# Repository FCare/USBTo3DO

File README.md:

# USBTo3DO
Connecting USB controller to the 3do

## Goal of the project
Plug a set of modern controllers to an original 3DO to emulate D-Pad, FlightStick and mouse.
Still support original 3DO controllers using daisy chain.

## License
The full project is delivered under MIT License.
You can fork, build, even sell this if you wants to.

## Need more info
I may organize some batches for interested users which can not build it themselves.
If you are interested, you can mail to usb23do@gmail.com
Be sure that you can have one the controller listed here. Adding more controller is not guaranteed.

## Supported controllers
 - **D-Pad**
	 - Any HID Gamepad/joystick class device shall work with a default mapping.
	 - Xbox360 wired controllers is supported.
	 - Xbox360 wireless controller is supported using a USB wireless adapter (https://aliexpress.com/item/1005004013649915.html)
	  > As button layout is not standard, a [specific mapper can be implemented](#dedicated_mapping).
 - **Mouse**
	 - Any USB mouse with an HID descriptor might work as mouse.
 - **FlightStick**
	  > As there is no way from the HID decriptor to determine if a controler is a flightstick or a standard controler, a [specific mapper has to be implemented](#dedicated_mapping)
 - **Wheel**
	  > Even if 3DO did not get any wheel controller, USB23DO support some controler as wheel (no throttle), mostly for Need For speed game. This support requires a [specific mapper to be implemented](#dedicated_mapping)

## List of tested USB controllers
 - **D-Pad**
   - Sixaxis PS3 controller (Wired) (https://en.wikipedia.org/wiki/Sixaxis)
   - DualShock4 PS4 controller (Wired) (https://fr.wikipedia.org/wiki/DualShock)
   - Xbox 360 wirless controllers using a USB PC receiver (https://aliexpress.com/item/1005004013649915.html)
   - 8BitDo M30 controller (https://www.8bitdo.com/m30/)
   - Retrobit Saturn controller (https://retro-bit.com/sega-collaboration/#saturn2-4)
   - Classical WII controllers with USB adapter (https://www.mayflash.com/product/showproduct.php?id=21)
   - Orignial sega saturn controller with adapter (https://www.mayflash.com/product/showproduct.php?id=20)
   - Known issues on 8bitDo USB wireless adapter2, Logitech gamepad F310 and 8bitDo SN30 pro (https://www.8bitdo.com/sn30-pro-usb-gamepad/)
 - **Mouse**
   - a large set of USB mouse
 - **FlightStick**
   - Thrustmaster T-Flight Hotas X (https://shop.thrustmaster.com/fr_fr/t-flight-hotas-x.html)
   - Thrustmaster T-Flight Stick X (https://www.thrustmaster.com/fr-fr/products/t-flight-stick-x)
   - Logitech Extreme 3D Pro (https://www.logitechg.com/fr-fr/products/space/extreme-3d-pro-joystick.942-000031.html)
 - **Wheel**
   - Thrustmaster T80 (https://www.thrustmaster.com/fr-fr/products/t80-ferrari-488-gtb-edition)
 
As of today, it does not support USB HUB. So if you are using a wired controller, you will need an adapter per wired controller. When you plug a USB adpater able to handle multiple controller (like wii adapater, saturn adapter or Xbox360 wireless receiver), then you can connect multiples controllers.

In case you installed the daisy chain connector, you can plug other USB adaptors or original controllers, Daisy chain will work.

## Videos
- [**D-Pad**](https://www.youtube.com/watch?v=yVEVkbPncLI&t=19)
- [**Mouse**](https://www.youtube.com/watch?v=dmMzbSZ1rbM&t=14)
- [**FlightStick**](https://www.youtube.com/watch?v=JpNO-n8_HC8&t=34)
- [**Wheel**](https://www.youtube.com/watch?v=EjhhHNndm9Q)

## What is required
 - PCB as provided in this git project. (You can order to shops like [JLCPCB](https://jlcpcb.com) using the [gerber files provided](https://github.com/FCare/USBTo3DO/blob/release/PCB/Gerber/USB23DO_2022-11-05.zip)
 - One femelle DB9 connector (to connect to the 3do or to the previous controller)
 - One male DB9 (optional) to continue the controller daisy chain
 - One Waveshare rp2040 zero (https://www.waveshare.com/rp2040-zero.htm)
 - a 4 way level shihter (https://aliexpress.com/item/32771873030.html)
 - a 4.7uF - 10v capacitor
 - a DB9 cable extension (https://aliexpress.com/item/4000095438635.html)

Here is a picture of the v1.1 PCB:  

## How to add a dedicated mapping
In order to add a specific mapping, you have to edit hid_gamepad.c or vendor_gamepad.c and add in the map array the VID, PID and corresponding mapping function. Once this is done, you have to compile a new FW and update the RP2040 device.

## How to compile
 - Tested on UBUNTU 20.04

 `git clone https://github.com/FCare/USBTo3DO.git`  
 `cd USBTo3DO`  
 `git submodule update --init --recursive`  
 `mkdir build;cd build`  
 `cmake ../`  
 `make -j16`  
 
 then flash RP2040 with the built uf2 file.

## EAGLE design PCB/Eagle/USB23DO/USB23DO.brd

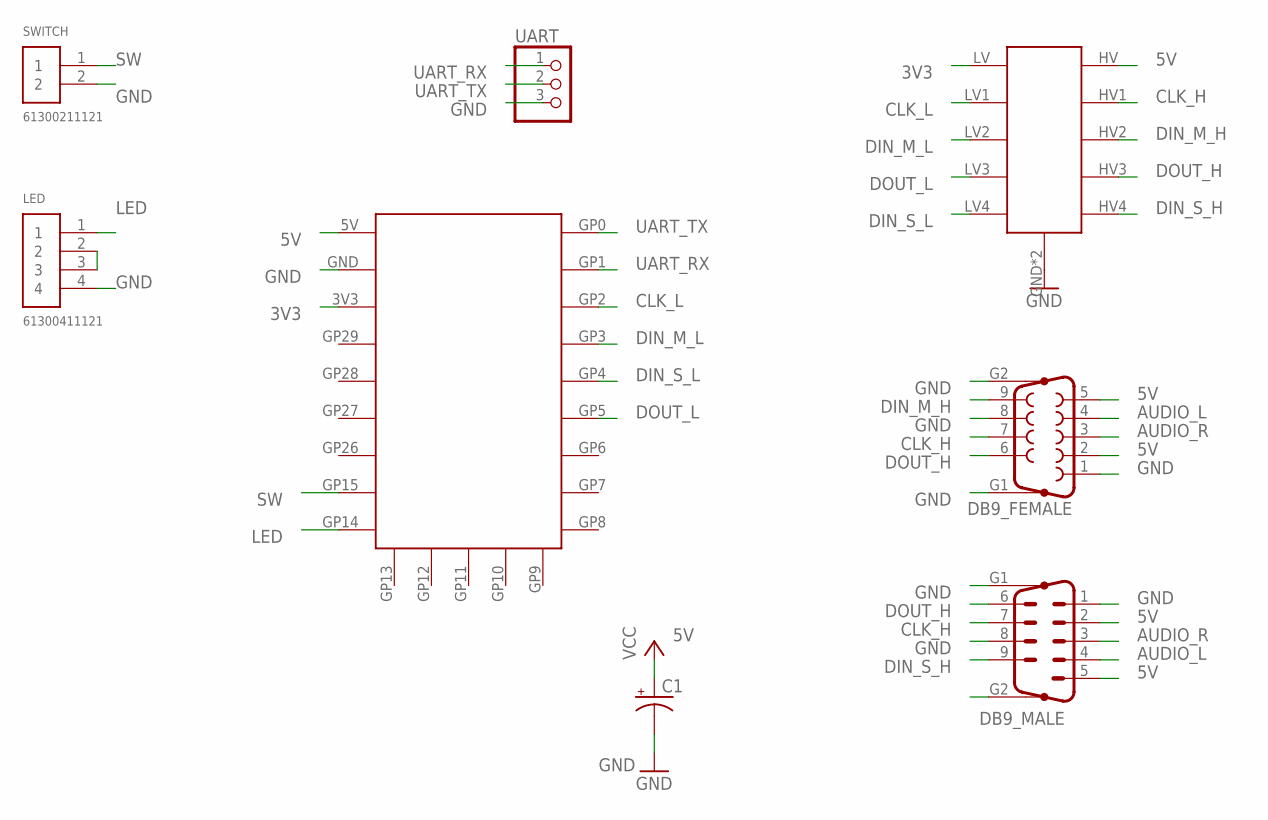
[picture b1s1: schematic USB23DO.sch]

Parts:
C1: CPOL-USB45181A; B45181A
DB9_FEMALE: F09HP
DB9_MALE: M09HP
LED: 61300411121
LVL_SHIFTER: 4WAYS_LEVEL_SHIFTER
RP2040-ZERO: WAVESHARE_RP_2040_ZERO
SWITCH: 61300211121
UART: PINHD-1X3CB; 1X03-CLEANBIG

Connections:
3V3: LVL_SHIFTER.LV, RP2040-ZERO.3V3
5V: C1.+, DB9_FEMALE.2, DB9_FEMALE.5, DB9_MALE.2, DB9_MALE.5, LVL_SHIFTER.HV, RP2040-ZERO.5V
AUDIO_L: DB9_FEMALE.4, DB9_MALE.4
AUDIO_R: DB9_FEMALE.3, DB9_MALE.3
CLK_H: DB9_FEMALE.7, DB9_MALE.7, LVL_SHIFTER.HV1
CLK_L: LVL_SHIFTER.LV1, RP2040-ZERO.GP2
DIN_M_H: DB9_FEMALE.9, LVL_SHIFTER.HV2
DIN_M_L: LVL_SHIFTER.LV2, RP2040-ZERO.GP3
DIN_S_H: DB9_MALE.9, LVL_SHIFTER.HV4
DIN_S_L: LVL_SHIFTER.LV4, RP2040-ZERO.GP4
DOUT_H: DB9_FEMALE.6, DB9_MALE.6, LVL_SHIFTER.HV3
DOUT_L: LVL_SHIFTER.LV3, RP2040-ZERO.GP5
GND: C1.-, DB9_FEMALE.1, DB9_FEMALE.8, DB9_FEMALE.G1, DB9_FEMALE.G2, DB9_MALE.1, DB9_MALE.8, DB9_MALE.G1, LED.4, LVL_SHIFTER.GND, LVL_SHIFTER.GND_1 (GND), RP2040-ZERO.GND, SWITCH.2, UART.3
LED: LED.1, RP2040-ZERO.GP14
unnamed: LED.2, LED.3
SW: RP2040-ZERO.GP15, SWITCH.1
UART_RX: RP2040-ZERO.GP1, UART.1
UART_TX: RP2040-ZERO.GP0, UART.2

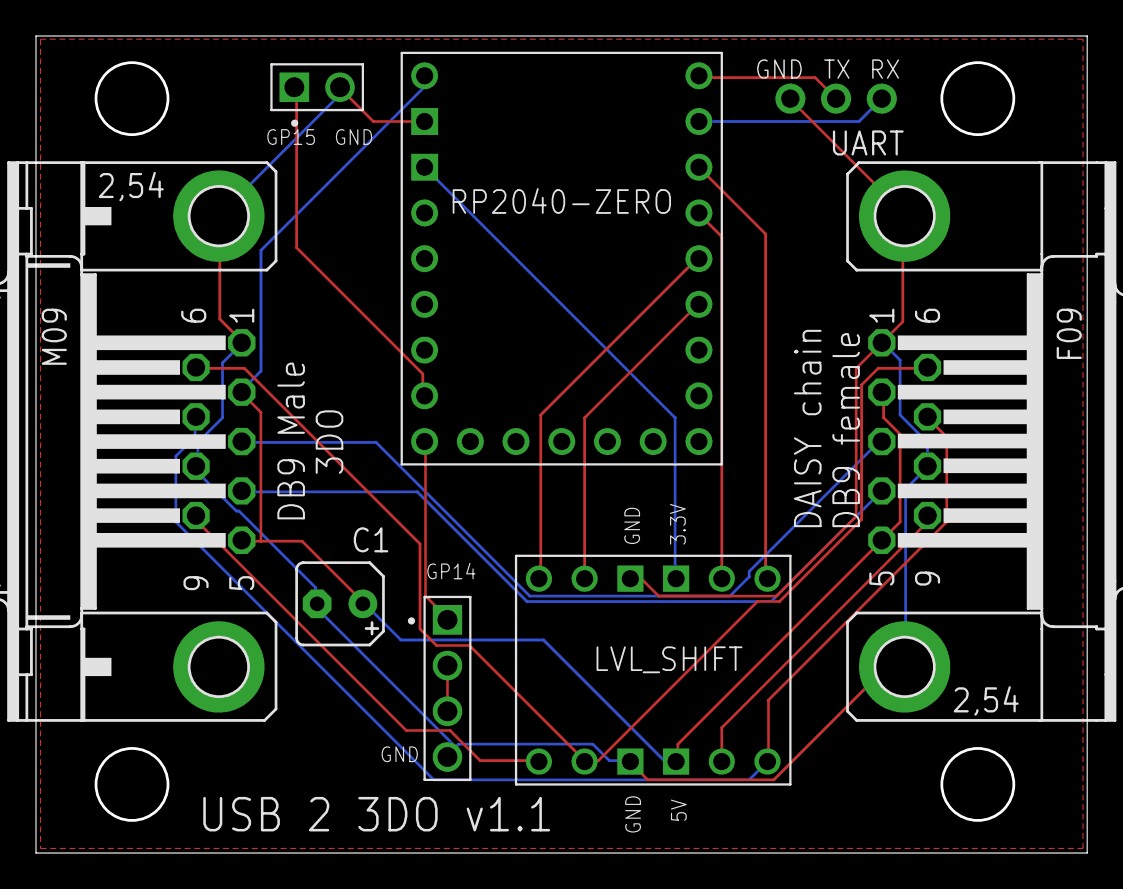
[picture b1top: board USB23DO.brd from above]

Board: 2 copper layers, 58.2 x 45.2 mm, 8 parts (0 on the bottom side), 18 nets.

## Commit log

2022-02-15 Add initial files
2022-02-15 Start the RP2040-LCD-0.96-M module with screen
2022-02-15 ignore pico-sdk modifications
2022-02-15 First drop of USB host
2022-02-15 Enable USB_HOst with Dualshock4 support
2022-02-15 Cleanup LCD code
2022-02-16 Add first gamepad reports for xbox 360 controllers
2022-02-16 Use personnal tinyUSB for xbox360 gamepad support
2022-02-16 Separate HID based gamepad and vendor specific gamepad
2022-02-17 Add button mapper for 8bitDo controller
2022-02-17 Set the pico board
2022-02-17 continue on HID report - right now no report callback...
2022-02-18 Update gameapad support
2022-02-18 fix 3do report - Too slow when based on GPIO. Have to move to SPI
2022-02-18 add missing files
2022-02-25 Cleanup - refacto
2022-02-25 fix compilation warnings
2022-02-25 Add dragonrise controller as HID input - used by cheap USB saturn controller
2022-02-25 Add some skeletons - Wii adapter support two controllers at the same time so need to implement multiple report id support. RetroBit mapping is not done. globally it will be better to handle the raw r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
2022-03-07 Support up to 9 controlers
2022-03-07 Add daisy chain support
2022-03-08 Clean up
2022-03-08 Fix dragonRise gamepad
2022-03-08 Add retro-bit controllers
2022-03-08 Add sega saturn controlers through usb adapter
2022-03-08 Add Playstation Classic usb controlers
2022-03-11 Add xbox360 wireless controler with usb PC wireless gaming
2022-03-11 Improve descriptor buffer
2022-03-11 Add led for xbox360
2022-03-11 Update tinyusb
2022-03-11 Add xbox360 wirless controler
2022-03-13 Do not trace - Fix xbox360 wireless receiver report: only report a present controler once we get the presence report or a valid report
2022-03-13 rename project name
2022-03-13 Add support for 8bitDo, retrobit, Xbox360 wired and some other cheap USB controlers
    ignore pico-sdk modifications
    First drop of USB host
    Enable USB_HOst with Dualshock4 support
    Cleanup LCD code
    Add first gamepad reports for xbox 360 controllers
    Use personnal tinyUSB for xbox360 gamepad support
2022-03-14 Add PCB files
    Zip can be used to order PCB on JLCPCB
    To edit, EAgle compatbile files are provided
2022-03-14 Add v1.0 PCB photo
    This version has an issue with one of the DB9 connector and does not support extension like switch or led support.
2022-09-13 Do not send a default report after an error on mapper. It blocks flightstick mode detection in games like bladeforce
2022-09-13 Move to a more easy pio approach
2022-09-13 Add Thrustmaster Hotas X suuport as flight stick
2022-09-13 Prepare joystick support
2022-09-13 Use number of controller. Assume USB controllers are the first one
2022-09-13 Implement a transformation to emulate square joystick with circle one
2022-09-13 First analog mapping for xbox 360 controller
2022-09-13 Add an anlogic mode for flight and one for wheel. Switch on xbox360 is done by pressing mode button. Joypad->Flight->wheel mode
2022-09-13 Add a tick for led animation on controllers
2022-09-13 Add daisy chain suport on pio
2022-09-13 Immplement flight stick behavior on Xbox 360 controller. Need to press mode button to switch between stick and pad mode. X/D are mapped on left stick, Y is mapped on analog trigger. This is due to th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
2022-09-13 Add Thrustmaster T80 steering wheel support as flight stick for need for speed
2022-09-13 Add DualShock 4 support
2022-09-15 Add 8bitDO M30 support as Dinput mode
2022-09-15 Add x360 wired controller suupport
2022-09-28 Try to make 8bitDo snes working
2022-09-29 Add logitech extreme 3d Pro early suport
2022-09-29 Add an early HID parser to detect button mapping from HID descriptor
2022-10-06 Move to HID descriptor mapping mechanism
2022-10-06 Less verbosity
2022-10-06 Update tinyusb version
2022-10-06 Fix ds4 mapping
2022-10-06 Less warnings
2022-10-07 Add PS3 sixaxis controller
2022-10-12 Add 8bitDo SN30 pro support
2022-10-12 Less verbose
2022-10-14 Make xinput less exclusive with dpad on analog sticks
2022-10-14 Add mouse support
2022-11-05 Updating description
2022-11-05 Update README.md
    Add videos
2022-11-06 Fix T80 wheel
